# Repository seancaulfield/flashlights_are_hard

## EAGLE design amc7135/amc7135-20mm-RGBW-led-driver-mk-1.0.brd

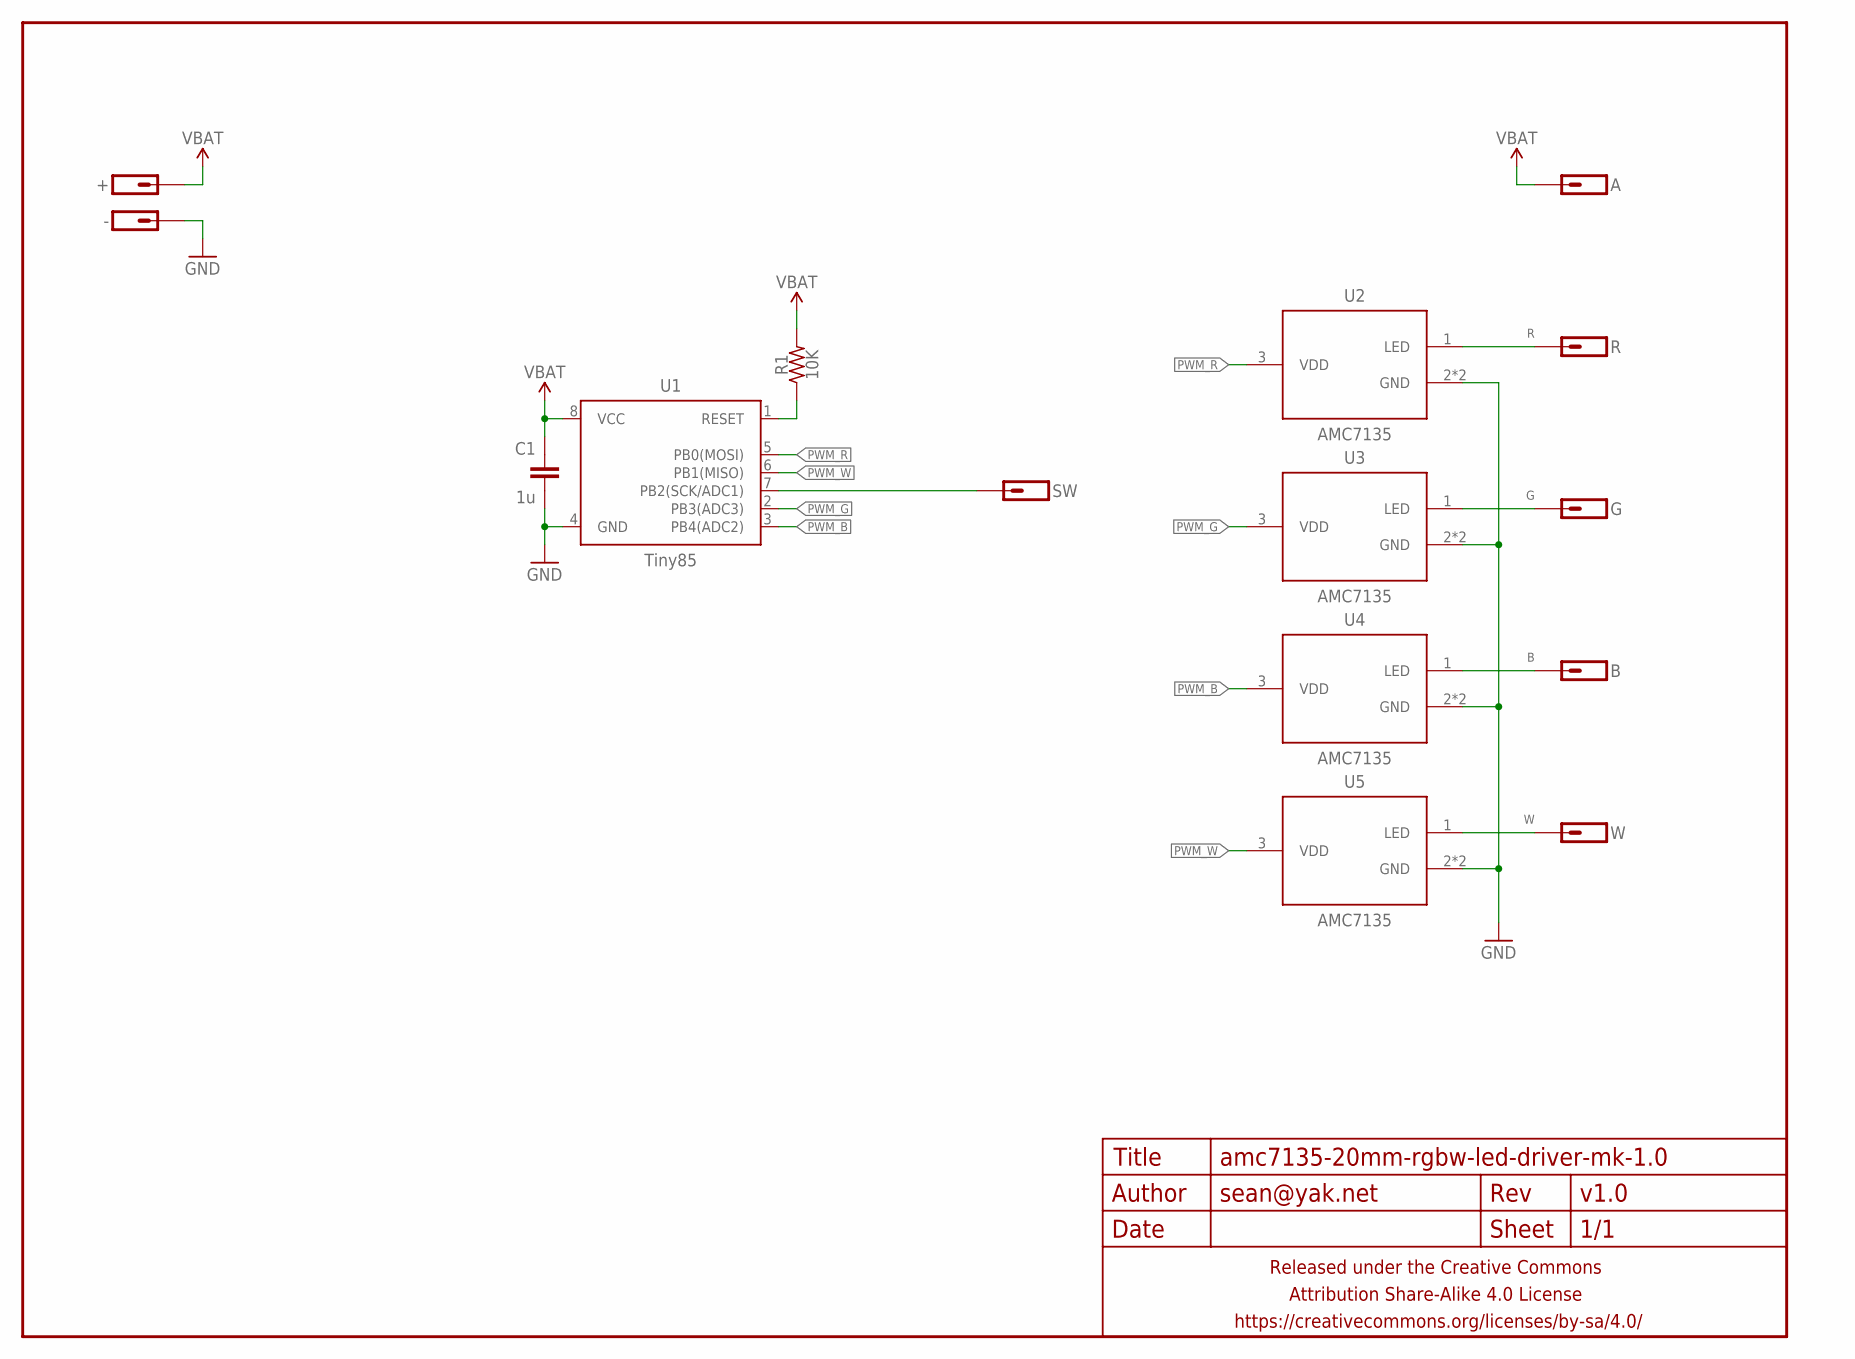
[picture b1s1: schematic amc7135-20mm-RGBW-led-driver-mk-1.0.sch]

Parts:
+: M01NOSTOP-CANTSTOP-DONTKNOWHOWTOSTOP; 1X01_SMD_NOSTOP_NOSILK
-: M01NOT-A-VIA-NOPE; 1X01_NOSILK_NOSTOP
A: M01PTH-1MM-CIR-NS; 1X01-1MM-CIR-NS
B: M01PTH-1MM-CIR-NS; 1X01-1MM-CIR-NS
C1: 1u; C0603-TIGHTER
FRAME1: FRAME-LETTERNO_PACKAGE; DUMMY
G: M01PTH-1MM-CIR-NS; 1X01-1MM-CIR-NS
R: M01PTH-1MM-CIR-NS; 1X01-1MM-CIR-NS
R1: 10K; R0603-TIGHTER
SW: M01PTH-0.8MM; 1X01-0.8MM
U1: Tiny85; SO08-EIAJ
U2, U3, U4, U5: AMC7135; SOT89
W: M01PTH-1MM-CIR-NS; 1X01-1MM-CIR-NS

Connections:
B: B.1, U4.1 (LED)
G: G.1, U3.1 (LED)
GND: -.P$1, C1.2, U1.4 (GND), U2.2 (GND), U2.4 (GND), U3.2 (GND), U3.4 (GND), U4.2 (GND), U4.4 (GND), U5.2 (GND), U5.4 (GND)
unnamed: SW.1, U1.7 (PB2(SCK/ADC1))
unnamed: R1.1, U1.1 (RESET)
PWM_B: U1.3 (PB4(ADC2)), U4.3 (VDD)
PWM_G: U1.2 (PB3(ADC3)), U3.3 (VDD)
PWM_R: U1.5 (PB0(MOSI)), U2.3 (VDD)
PWM_W: U1.6 (PB1(MISO)), U5.3 (VDD)
R: R.1, U2.1 (LED)
VBAT: +.1, A.1, C1.1, R1.2, U1.8 (VCC)
W: U5.1 (LED), W.1

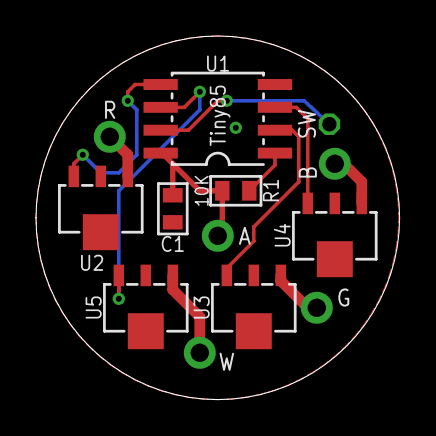
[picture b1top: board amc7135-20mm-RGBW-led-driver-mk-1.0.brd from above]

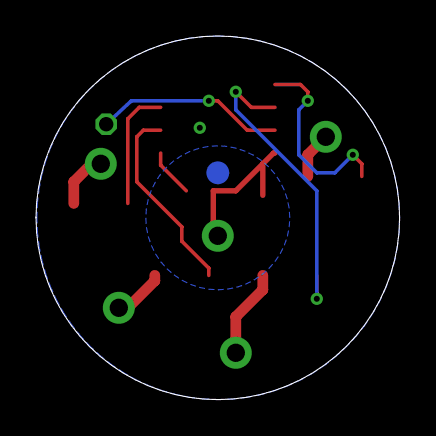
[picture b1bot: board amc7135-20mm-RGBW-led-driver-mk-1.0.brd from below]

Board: 2 copper layers, 20.2 x 20.2 mm, 16 parts (2 on the bottom side), 12 nets.

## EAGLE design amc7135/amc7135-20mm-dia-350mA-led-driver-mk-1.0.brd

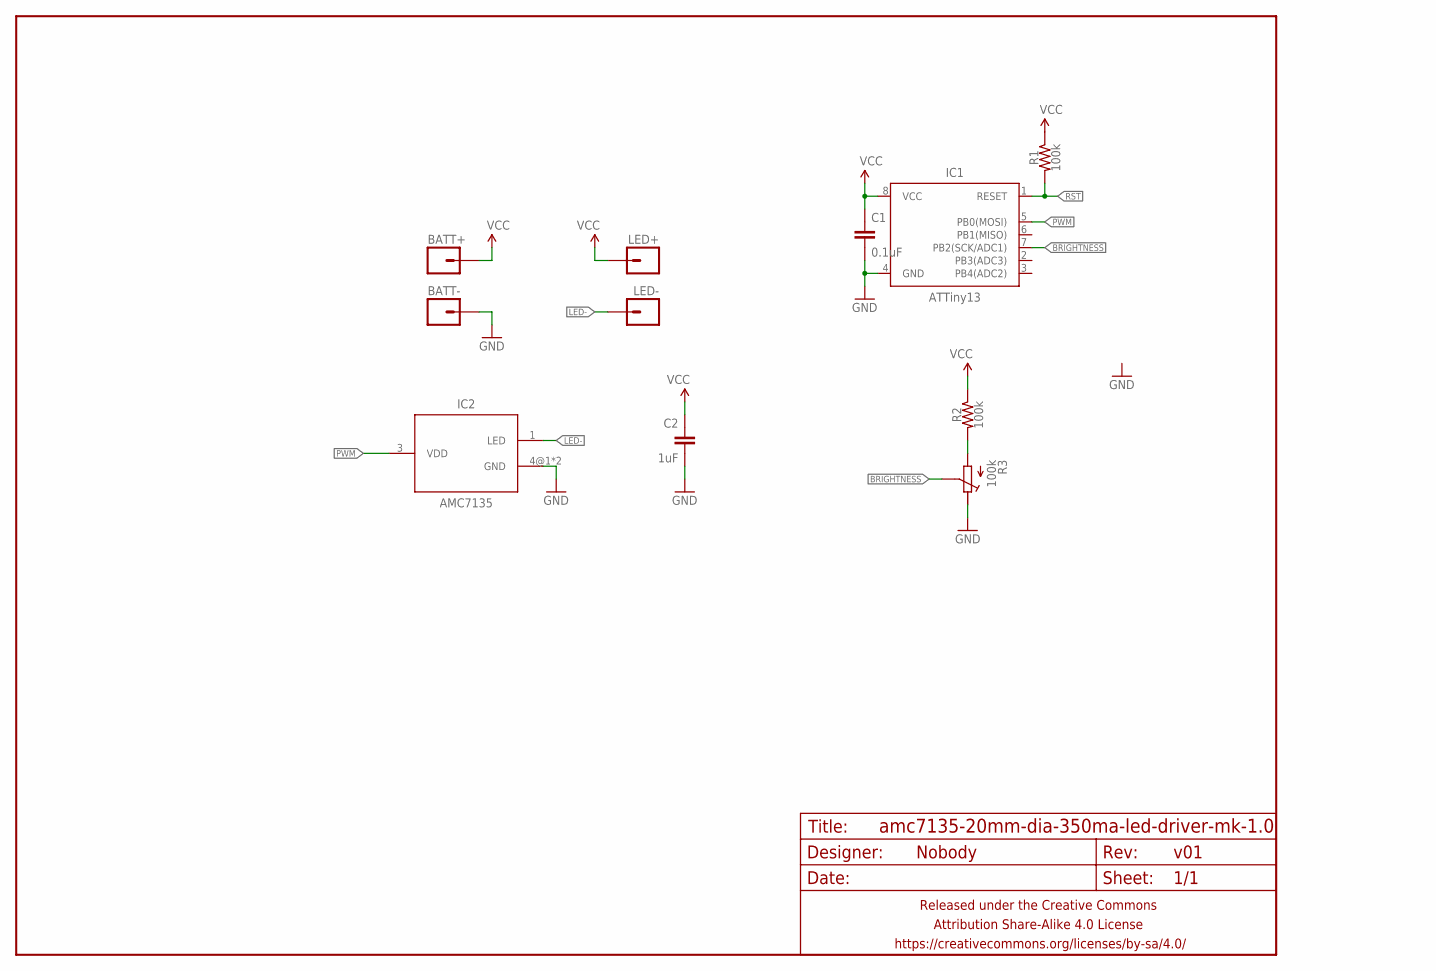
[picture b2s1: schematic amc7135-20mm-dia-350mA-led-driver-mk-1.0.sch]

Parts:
BATT+: M01NOT-A-VIA-NOPE; 1X01_NOSILK_NOSTOP
BATT-: M01NOT-A-VIA-NOPE; 1X01_NOSILK_NOSTOP
C1: 0.1uF; C0805
C2: 1uF; C1206
FRAME1: FRAME-LETTERNO_PACKAGE; DUMMY
IC1: ATTiny13; SO08
IC2: AMC7135; SOT89-NOTHERM
LED+: M01PTH-1.2MM; 1X01-1.2MM
LED-: M01PTH-1.2MM-NS; 1X01-1.2MM-NS
R1, R2: 100k; R0805
R3: 100k; EVM3Y

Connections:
BRIGHTNESS: IC1.7 (PB2(SCK/ADC1)), R3.S
GND: BATT-.P$1, C1.2, C2.2, IC1.4 (GND), IC2.4@1 (GND), IC2.4@2 (GND), R3.E
LED-: IC2.1 (LED), LED-.P$1
unnamed: R2.2, R3.A
PWM: IC1.5 (PB0(MOSI)), IC2.3 (VDD)
RST: IC1.1 (RESET), R1.2
VCC: BATT+.P$1, C1.1, C2.1, IC1.8 (VCC), LED+.P$1, R1.1, R2.1

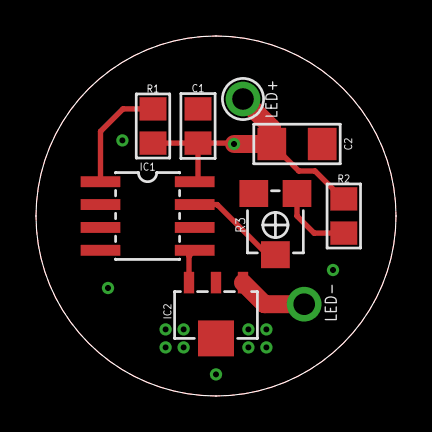
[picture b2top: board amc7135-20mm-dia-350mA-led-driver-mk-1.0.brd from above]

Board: 2 copper layers, 20.0 x 20.0 mm, 12 parts (0 on the bottom side), 7 nets.

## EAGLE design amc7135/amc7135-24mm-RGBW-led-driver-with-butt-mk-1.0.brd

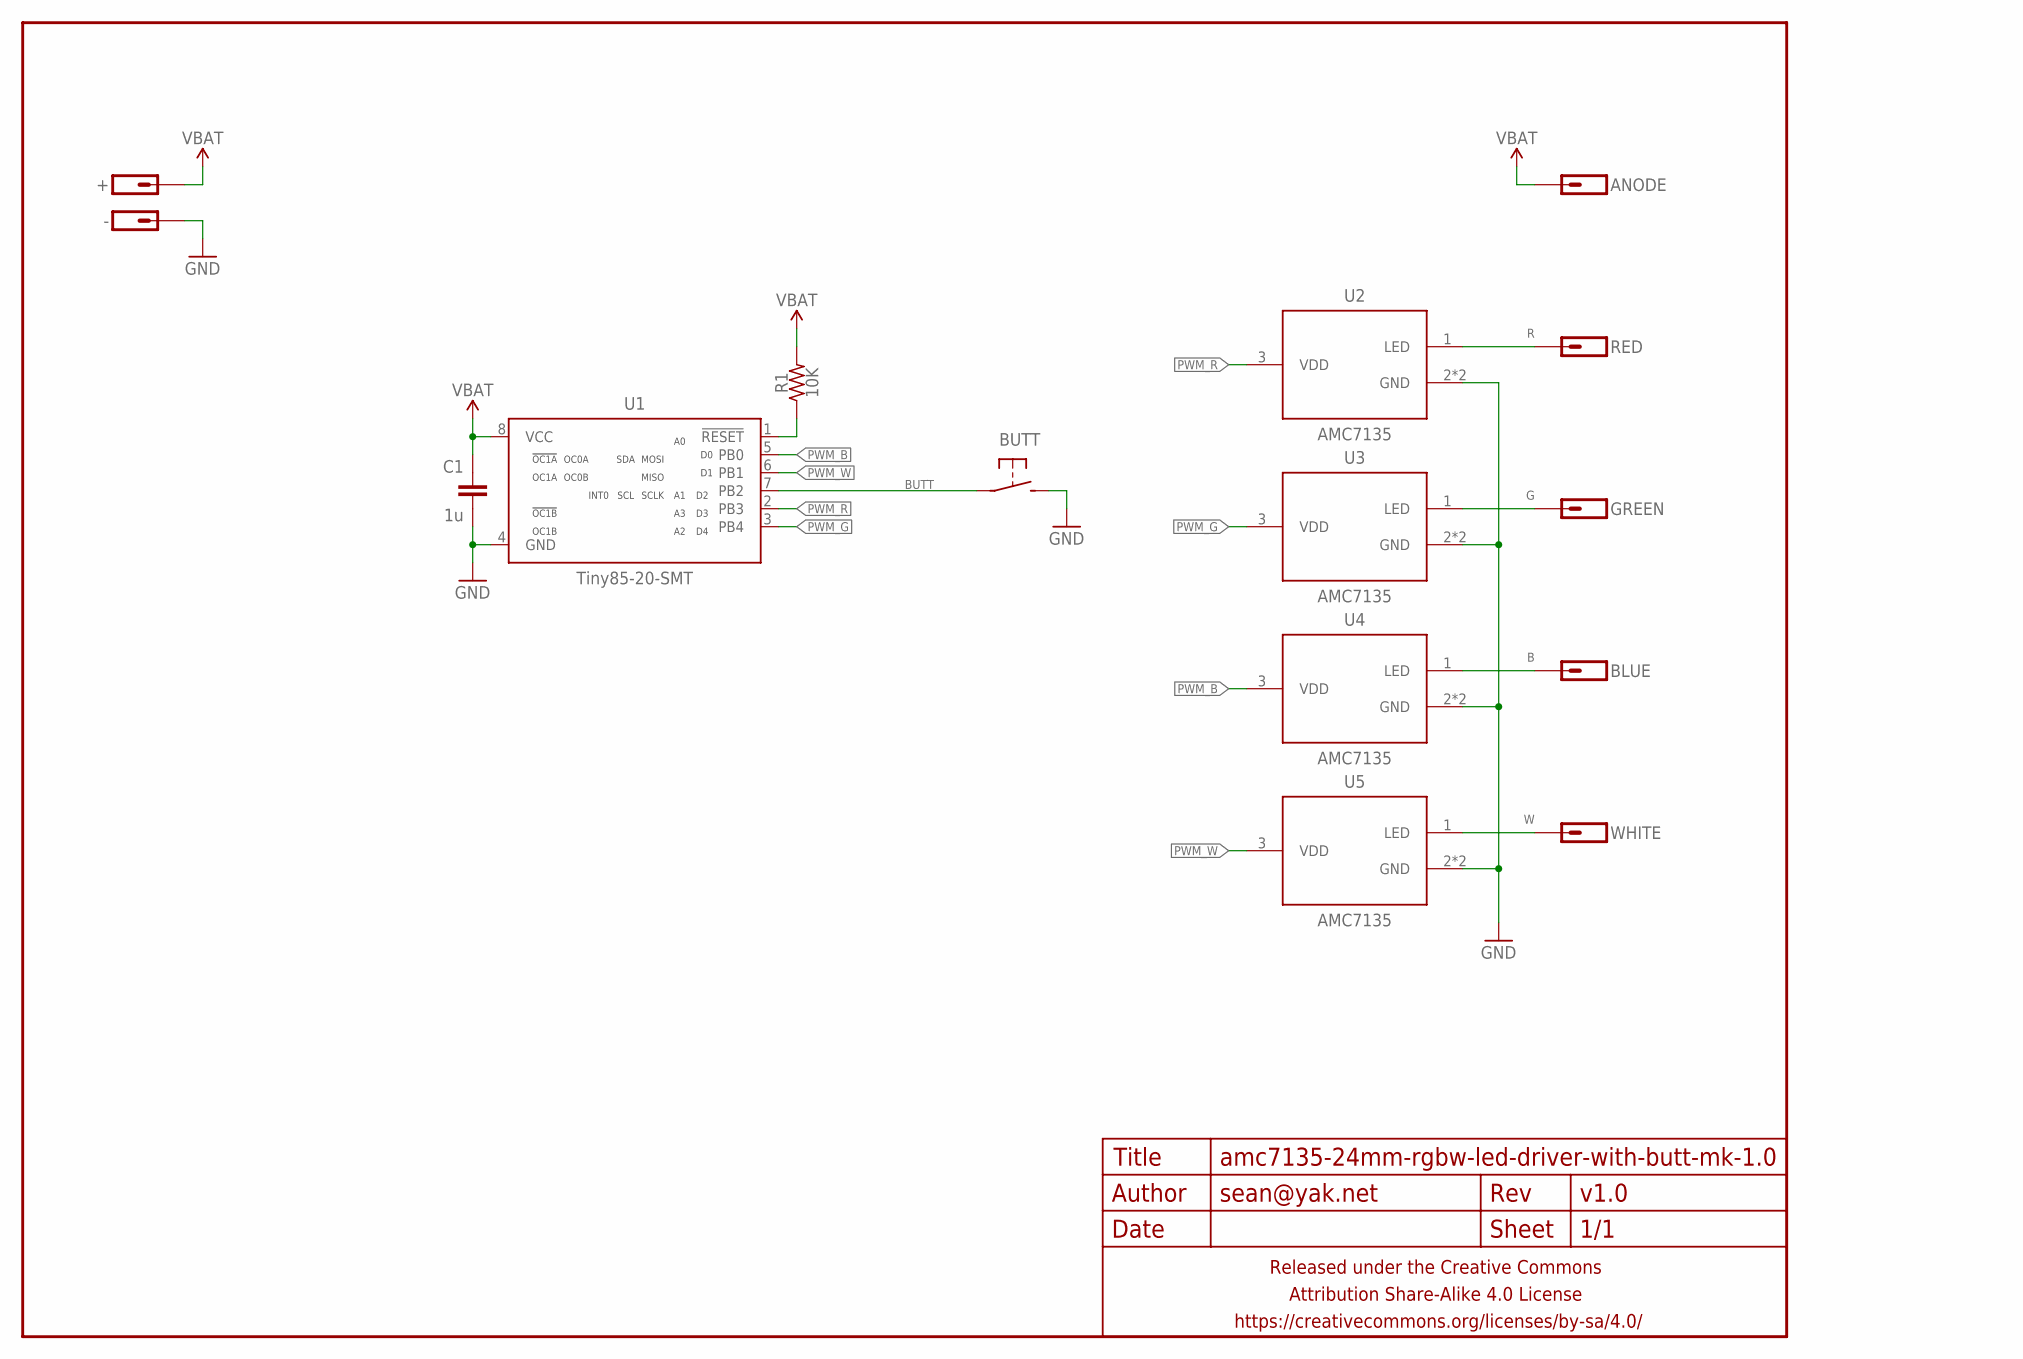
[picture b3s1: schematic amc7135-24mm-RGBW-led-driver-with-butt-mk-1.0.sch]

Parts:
+: M01NOSTOP-CANTSTOP-DONTKNOWHOWTOSTOP; 1X01_SMD_NOSTOP_NOSILK
-: M01NOT-A-VIA-NOPE; 1X01_NOSILK_NOSTOP
ANODE: M01PTH-1.2MM-NS; 1X01-1.2MM-NS
BLUE: M01PTH-1MM-CIR-NS; 1X01-1MM-CIR-NS
BUTT: SPST-NO-TACT3MM-RA; TACTILE-PTH-SIDE
C1: 1u; C0402
FRAME1: FRAME-LETTERNO_PACKAGE; DUMMY
GREEN: M01PTH-1MM-CIR-NS; 1X01-1MM-CIR-NS
R1: 10K; R0402
RED: M01PTH-1MM-CIR-NS; 1X01-1MM-CIR-NS
U1: Tiny85-20-SMT; SO08-EIAJ
U2, U3, U4, U5: AMC7135; SOT89
WHITE: M01PTH-1MM-CIR-NS; 1X01-1MM-CIR-NS

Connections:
B: BLUE.1, U4.1 (LED)
BUTT: BUTT.1, U1.7 (PB2)
G: GREEN.1, U3.1 (LED)
GND: -.P$1, BUTT.2, C1.2, U1.4 (GND), U2.2 (GND), U2.4 (GND), U3.2 (GND), U3.4 (GND), U4.2 (GND), U4.4 (GND), U5.2 (GND), U5.4 (GND)
unnamed: R1.1, U1.1 (!RESET)
PWM_B: U1.5 (PB0), U4.3 (VDD)
PWM_G: U1.3 (PB4), U3.3 (VDD)
PWM_R: U1.2 (PB3), U2.3 (VDD)
PWM_W: U1.6 (PB1), U5.3 (VDD)
R: RED.1, U2.1 (LED)
VBAT: +.1, ANODE.P$1, C1.1, R1.2, U1.8 (VCC)
W: U5.1 (LED), WHITE.1

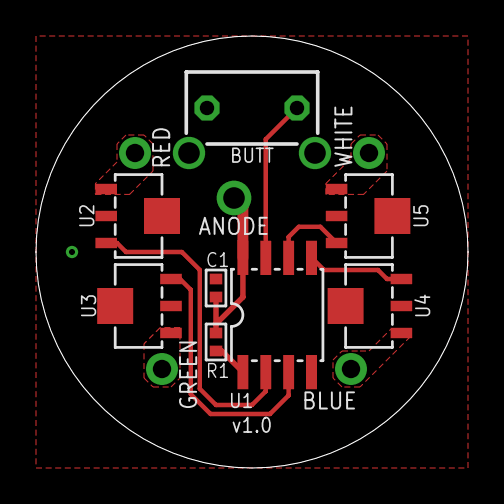
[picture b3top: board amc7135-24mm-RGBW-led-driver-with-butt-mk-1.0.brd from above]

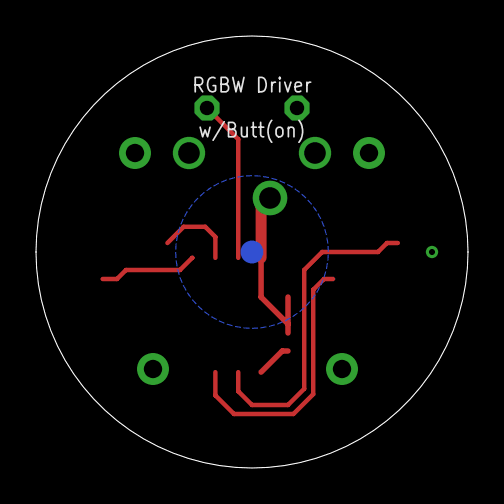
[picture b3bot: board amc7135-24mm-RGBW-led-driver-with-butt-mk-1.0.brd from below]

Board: 2 copper layers, 24.0 x 24.0 mm, 16 parts (2 on the bottom side), 12 nets.

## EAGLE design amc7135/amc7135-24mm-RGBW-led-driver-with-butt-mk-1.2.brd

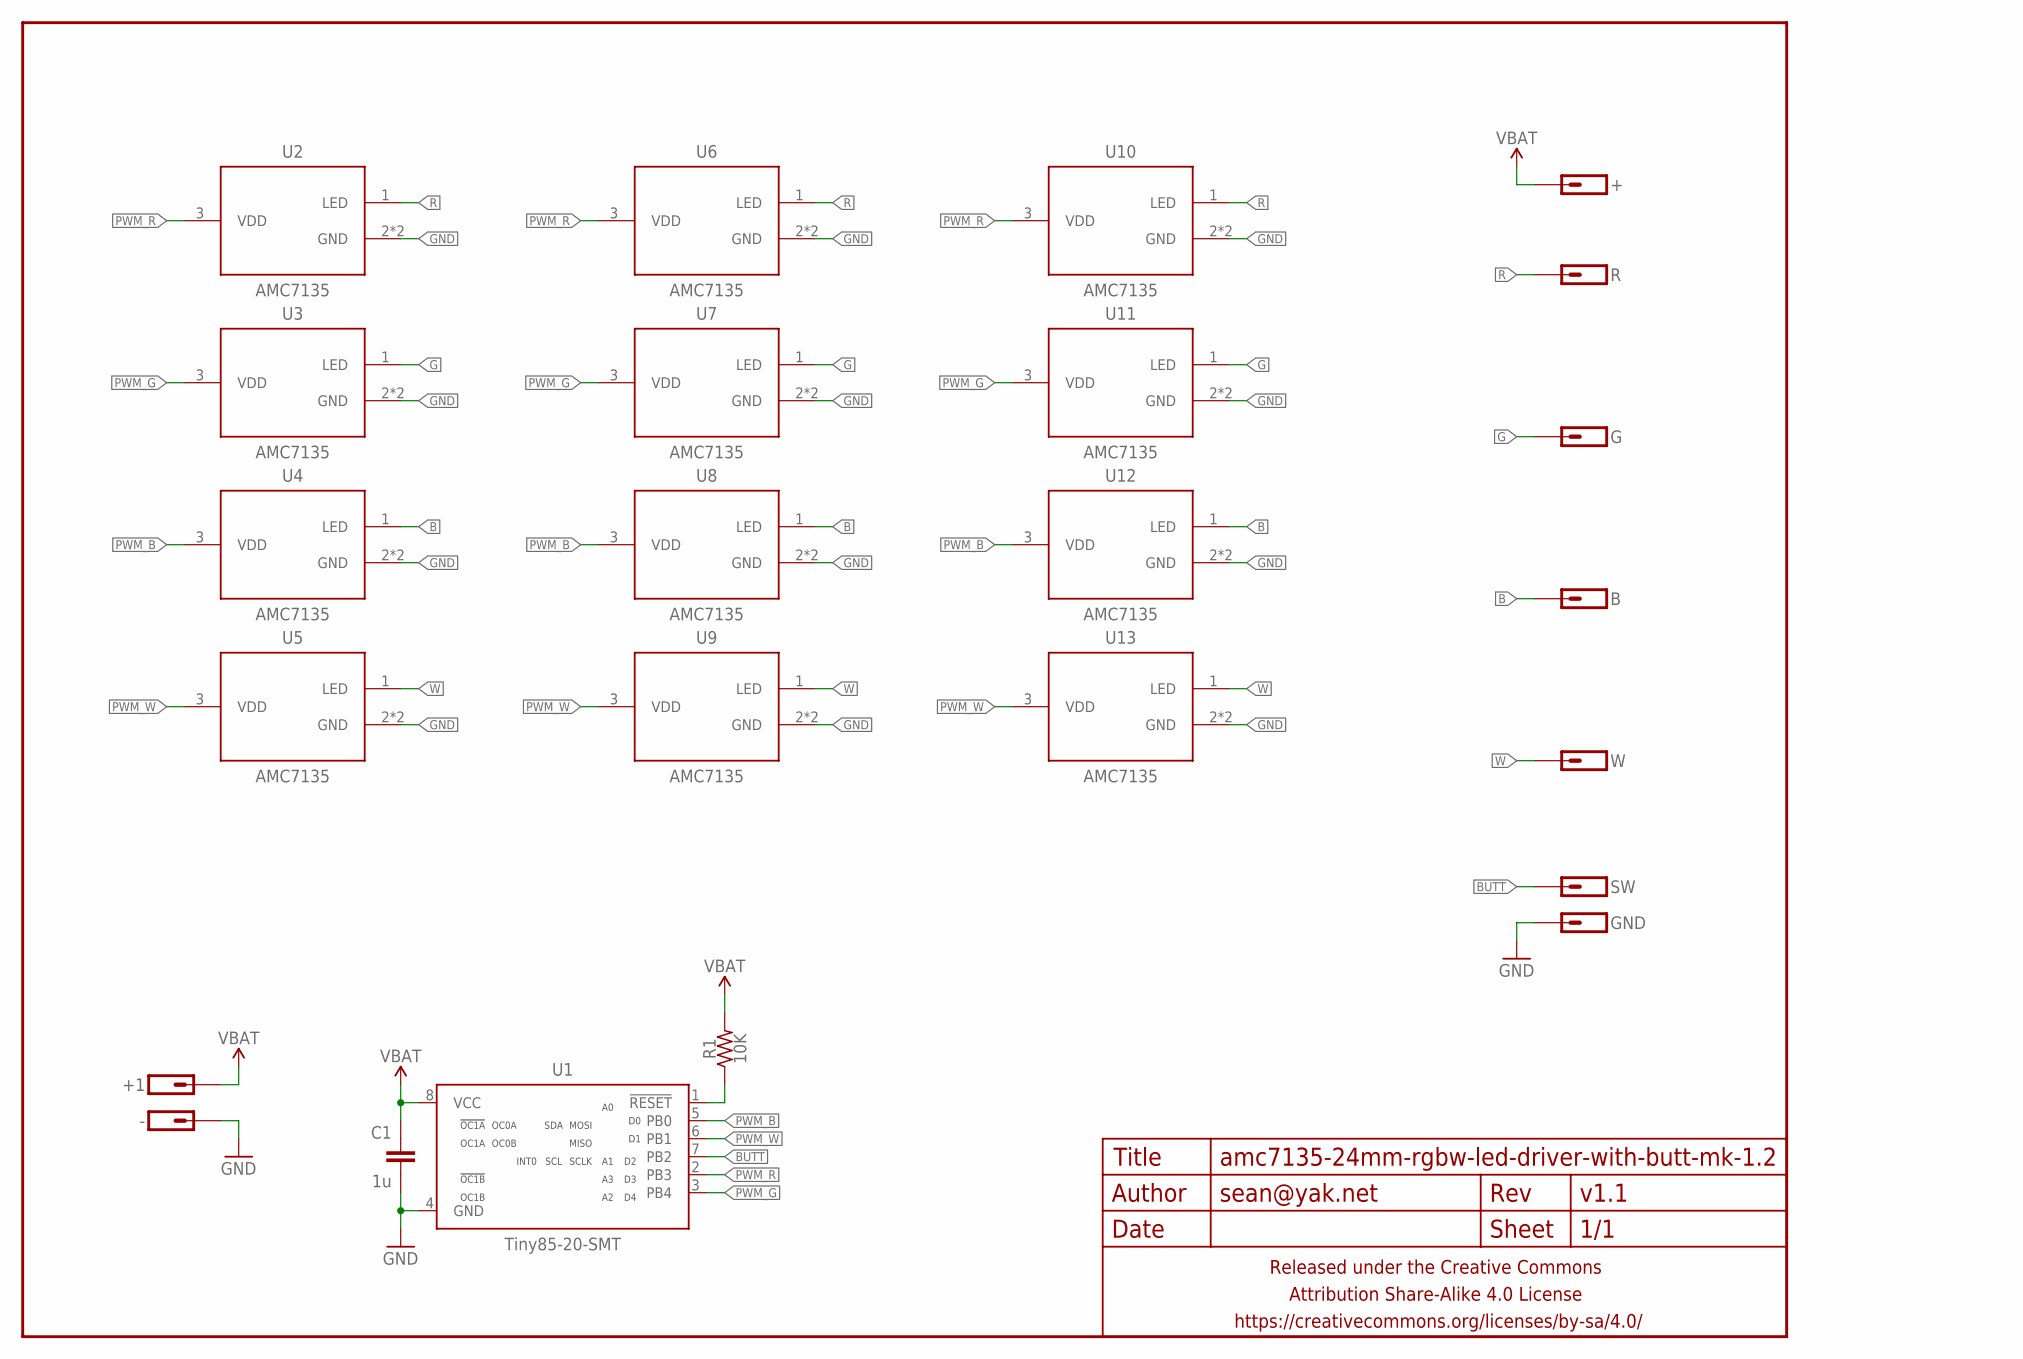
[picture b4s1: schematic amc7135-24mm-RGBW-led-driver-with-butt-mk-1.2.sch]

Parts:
+: M01PTH-1.2MM-NS; 1X01-1.2MM-NS
+1: M01NOSTOP-CANTSTOP-DONTKNOWHOWTOSTOP; 1X01_SMD_NOSTOP_NOSILK
-: M01NOT-A-VIA-NOPE; 1X01_NOSILK_NOSTOP
B: M01SMD-1.25MM-DIA; 1X01-SMD-1.25MM-DIA-NS
C1: 1u; C0603-TIGHTER
FRAME1: FRAME-LETTERNO_PACKAGE; DUMMY
G: M01SMD-1.25MM-DIA; 1X01-SMD-1.25MM-DIA-NS
GND: M01PTH-0.8MM; 1X01-0.8MM
R: M01SMD-1.25MM-DIA; 1X01-SMD-1.25MM-DIA-NS
R1: 10K; R0603-TIGHTER
SW: M01PTH-0.8MM; 1X01-0.8MM
U1: Tiny85-20-SMT; SO08-EIAJ
U2, U3, U4, U5, U6, U7, U8, U9, U10, U11, U12, U13: AMC7135; SOT89
W: M01SMD-1.25MM-DIA; 1X01-SMD-1.25MM-DIA-NS

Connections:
B: B.P$1, U8.1 (LED)
BUTT: SW.1, U1.7 (PB2)
G: G.P$1, U7.1 (LED)
GND: -.P$1, C1.2, GND.1, U1.4 (GND), U6.2 (GND), U6.4 (GND), U7.2 (GND), U7.4 (GND), U8.2 (GND), U8.4 (GND), U9.2 (GND), U9.4 (GND)
unnamed: R1.1, U1.1 (!RESET)
PWM_B: U1.5 (PB0), U4.3 (VDD), U8.3 (VDD), U12.3 (VDD)
PWM_G: U1.3 (PB4), U3.3 (VDD), U7.3 (VDD), U11.3 (VDD)
PWM_R: U1.2 (PB3), U2.3 (VDD), U6.3 (VDD), U10.3 (VDD)
PWM_W: U1.6 (PB1), U5.3 (VDD), U9.3 (VDD), U13.3 (VDD)
R: R.P$1, U6.1 (LED)
VBAT: +.P$1, +1.1, C1.1, R1.2, U1.8 (VCC)
W: U9.1 (LED), W.P$1

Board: 2 copper layers, 25 parts (2 on the bottom side), 12 nets, no tracks yet.

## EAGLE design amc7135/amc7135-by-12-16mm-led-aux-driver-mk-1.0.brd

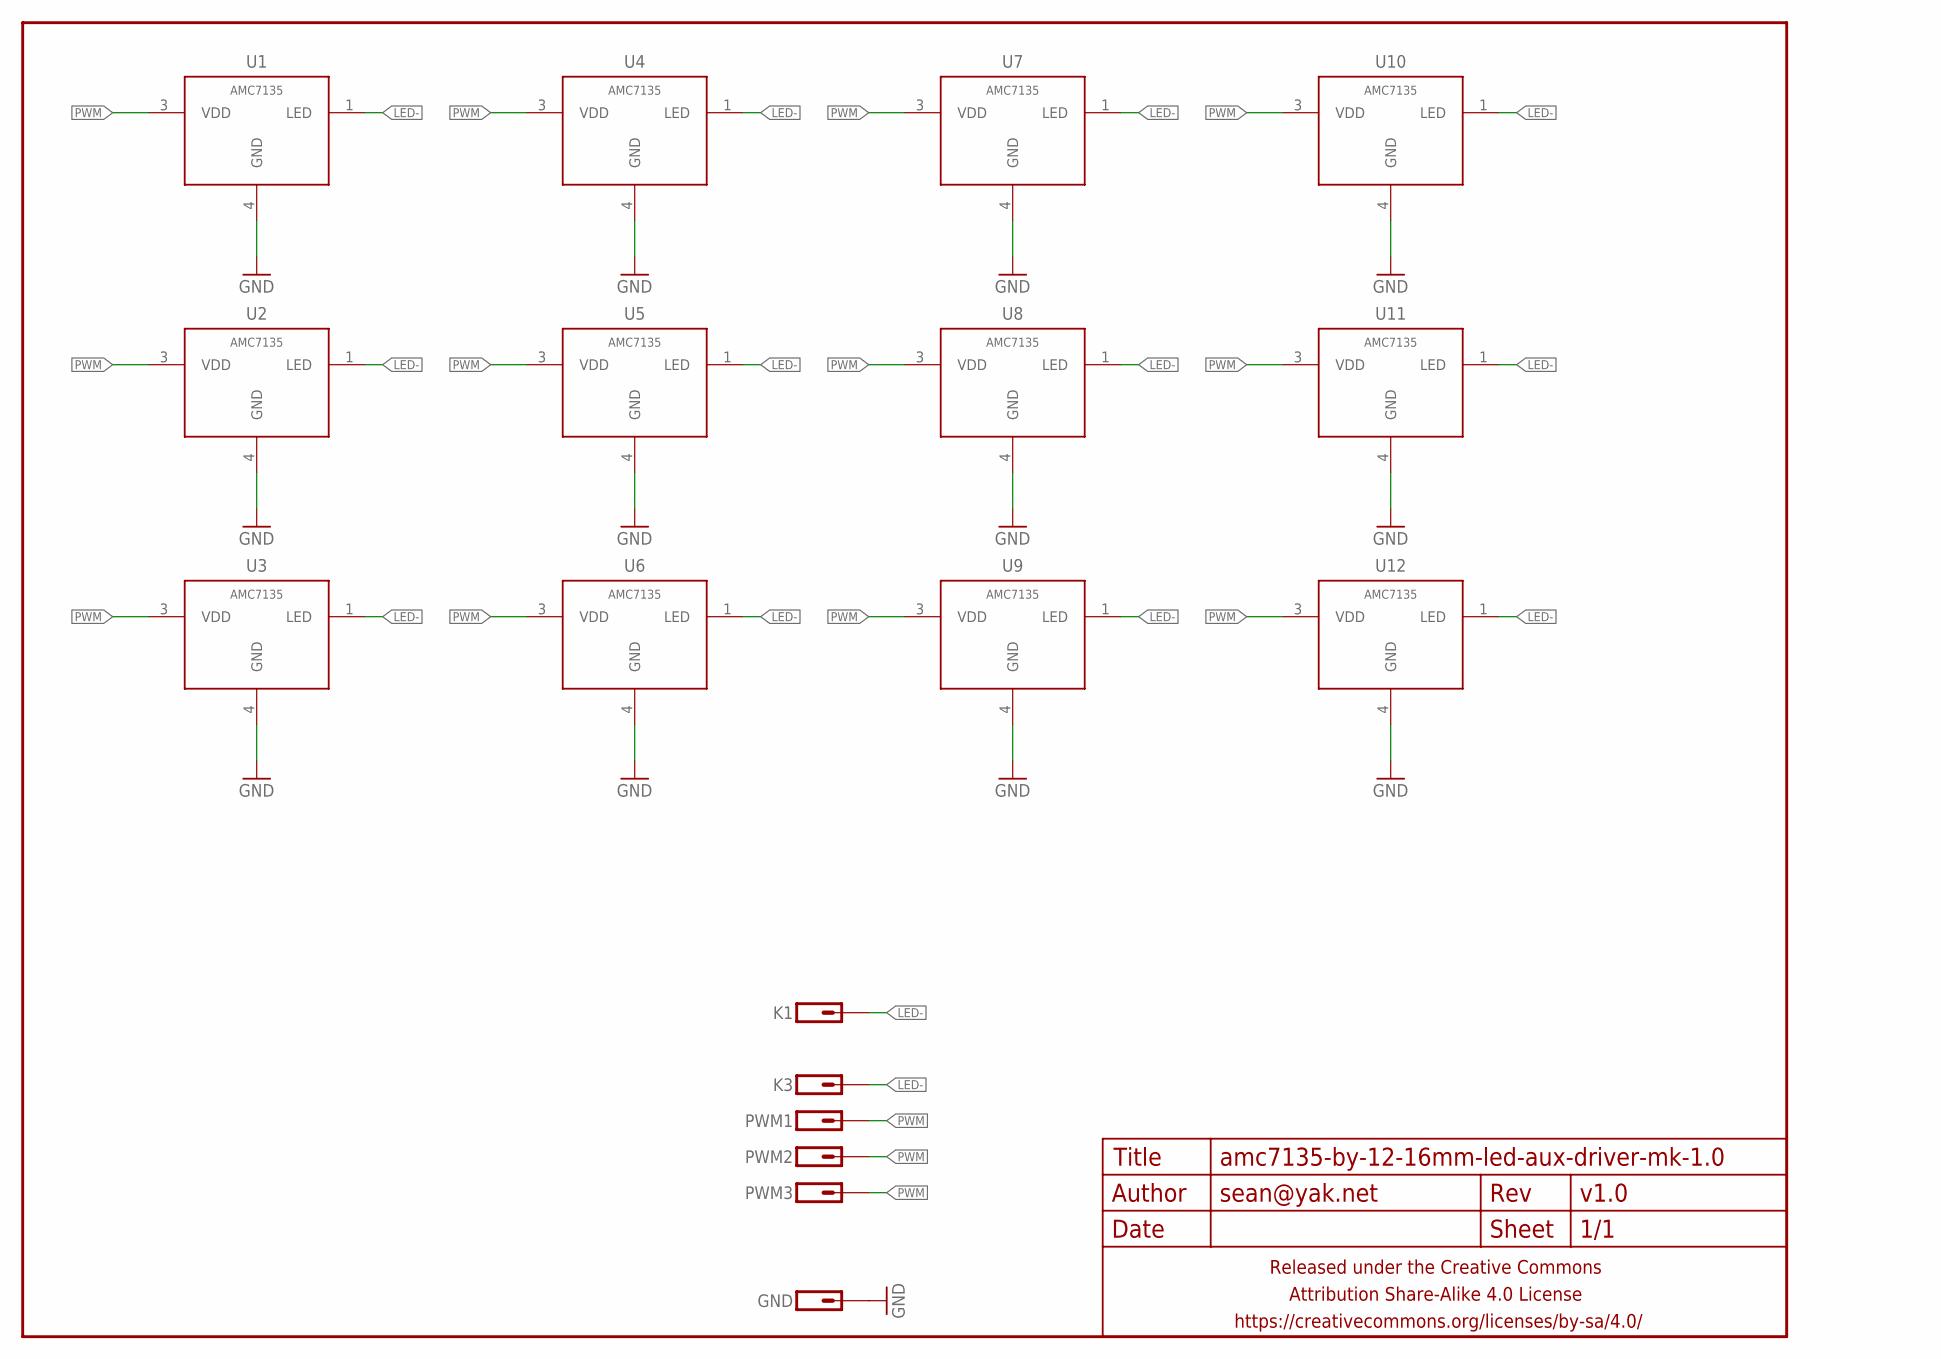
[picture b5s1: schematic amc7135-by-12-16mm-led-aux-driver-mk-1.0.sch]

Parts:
FRAME1: FRAME-LETTERNO_PACKAGE; DUMMY
GND: M01SMD-1MM-DIA-NS; 1X01-SMD-1MM-DIA-NS
K1: M011X01-0.9MM-CIR; 1X01-0.9MM-CIR
K3: M01SMD-1MM-DIA-NS; 1X01-SMD-1MM-DIA-NS
PWM1, PWM2: M01PTH-0.7MM; 1X01-0.7MM
PWM3: M01SMD-1MM-DIA-NS; 1X01-SMD-1MM-DIA-NS
U1, U2, U3, U4, U5, U6, U7, U8, U9, U10, U11, U12: AMC7135; SOT89-NOTHERM-ROUNDED-LESS

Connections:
GND: GND.P$1, U1.4 (GND), U2.4 (GND), U3.4 (GND), U4.4 (GND), U5.4 (GND), U6.4 (GND), U7.4 (GND), U8.4 (GND), U9.4 (GND), U10.4 (GND), U11.4 (GND), U12.4 (GND)
LED-: K1.P$1, K3.P$1, U1.1 (LED), U2.1 (LED), U3.1 (LED), U4.1 (LED), U5.1 (LED), U6.1 (LED), U7.1 (LED), U8.1 (LED), U9.1 (LED), U10.1 (LED), U11.1 (LED), U12.1 (LED)
PWM: PWM1.1, PWM2.1, PWM3.P$1, U1.3 (VDD), U2.3 (VDD), U3.3 (VDD), U4.3 (VDD), U5.3 (VDD), U6.3 (VDD), U7.3 (VDD), U8.3 (VDD), U9.3 (VDD), U10.3 (VDD), U11.3 (VDD), U12.3 (VDD)

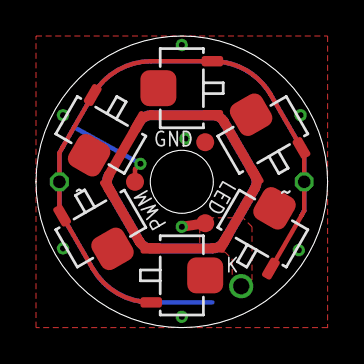
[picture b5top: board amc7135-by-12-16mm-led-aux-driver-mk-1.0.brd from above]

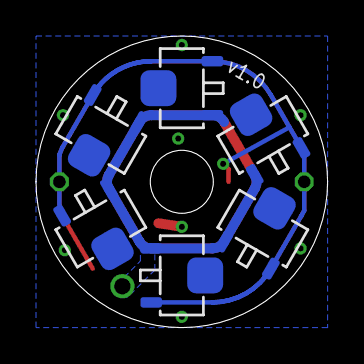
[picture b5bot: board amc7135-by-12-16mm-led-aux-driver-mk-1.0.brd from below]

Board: 2 copper layers, 16.2 x 16.2 mm, 19 parts (6 on the bottom side), 3 nets.

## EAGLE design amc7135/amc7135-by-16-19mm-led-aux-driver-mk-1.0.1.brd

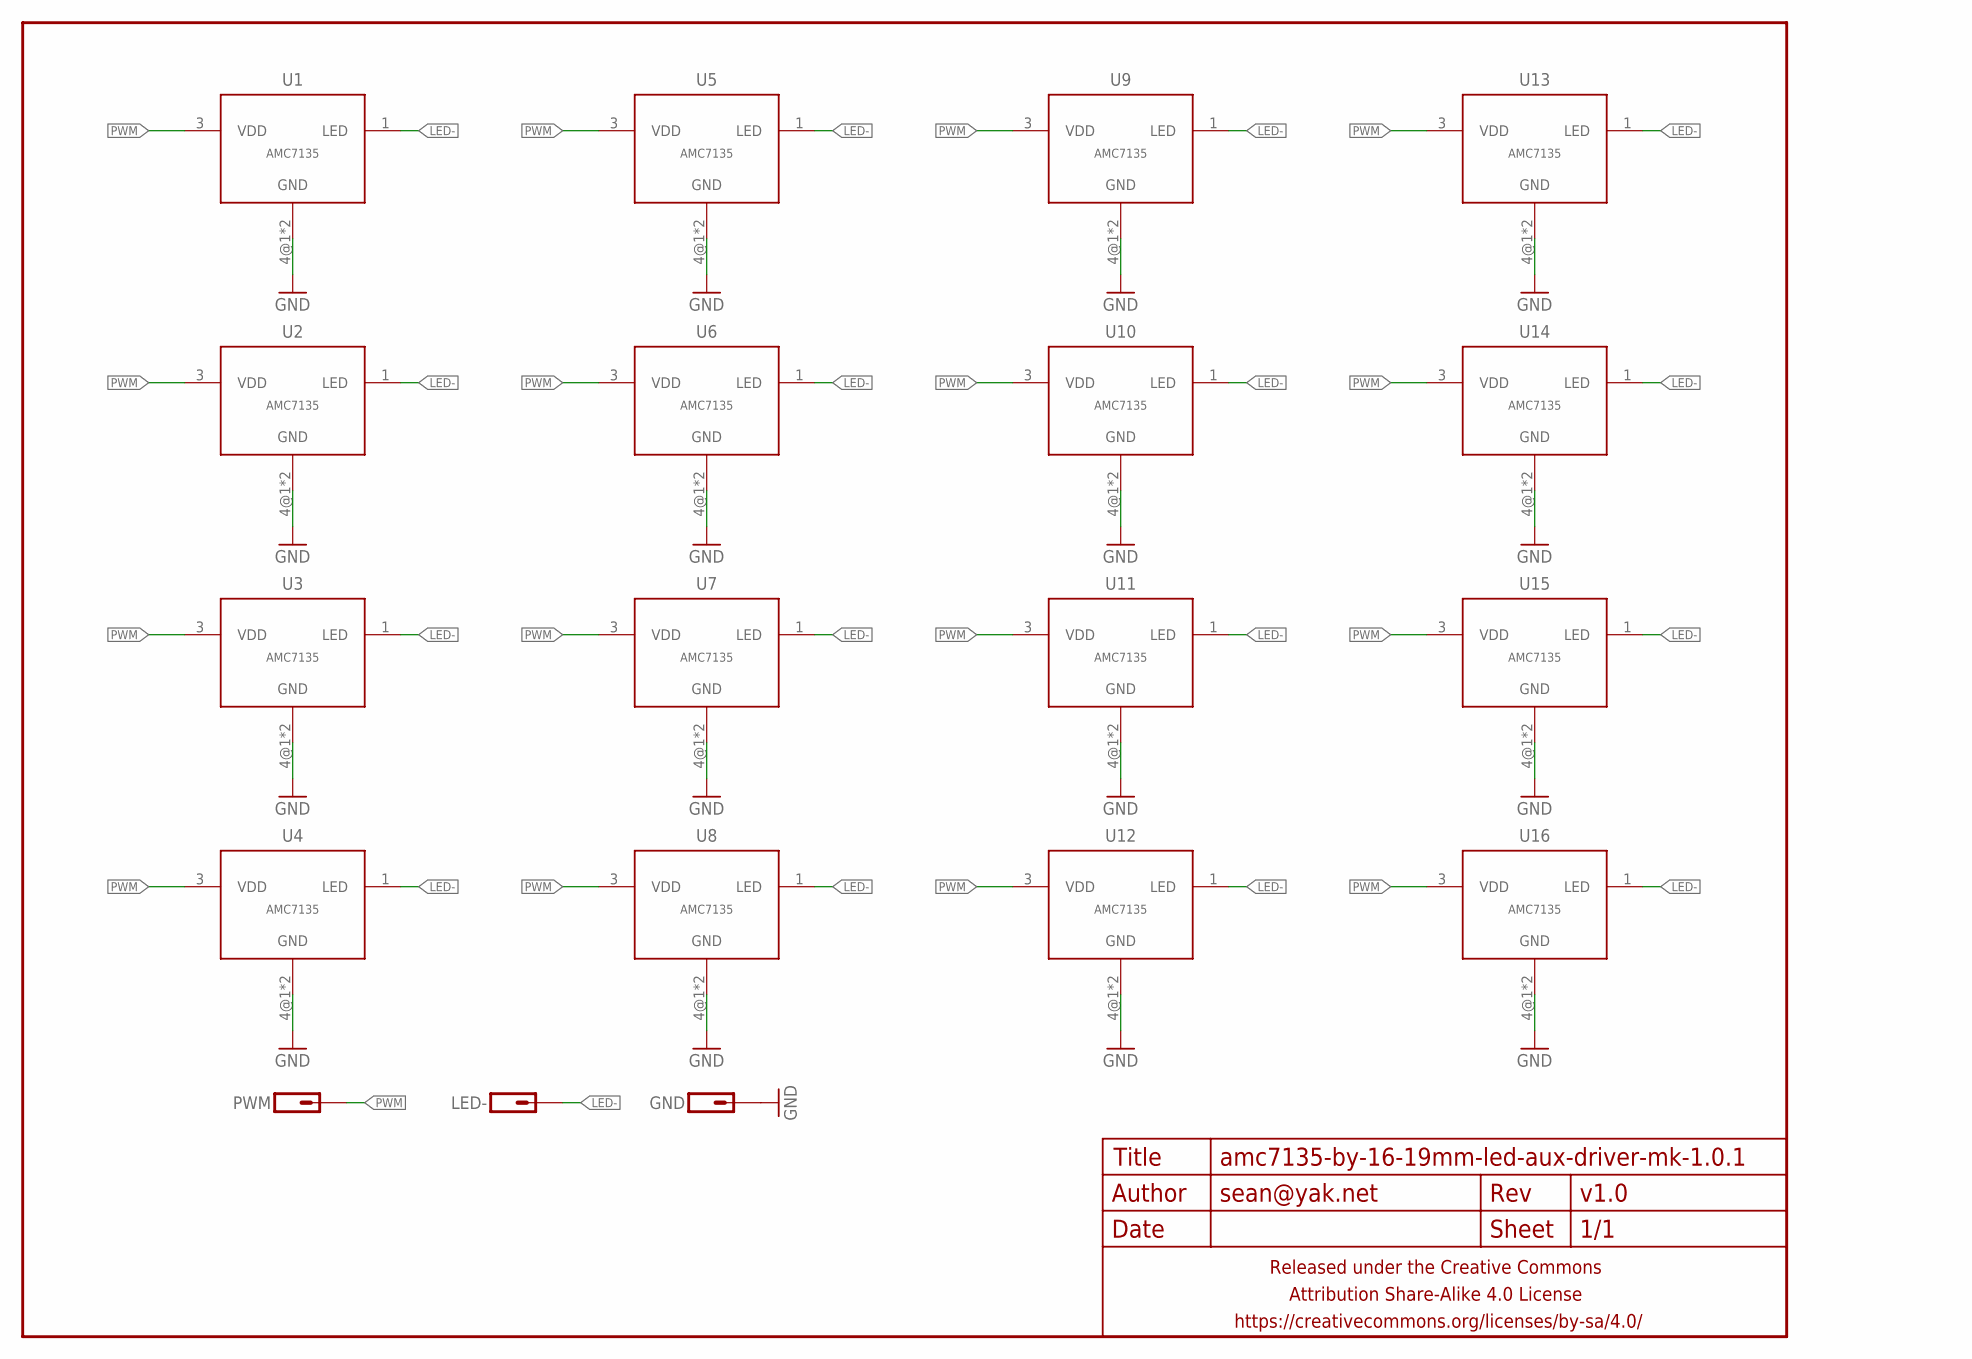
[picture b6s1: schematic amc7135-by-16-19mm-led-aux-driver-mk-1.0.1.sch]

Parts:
FRAME1: FRAME-LETTERNO_PACKAGE; DUMMY
GND: M01PTH-1.2MM-NS; 1X01-1.2MM-NS
LED-: M01PTH-1.2MM-NS; 1X01-1.2MM-NS
PWM: M01PTH-0.9MM-CIR; 1X01-0.9MM-CIR
U1, U2, U3, U4, U5, U6, U7, U8, U9, U10, U11, U12, U13, U14, U15, U16: AMC7135; SOT89-ROUNDED-SMALLER

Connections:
GND: GND.P$1, U1.4@1 (GND), U1.4@2 (GND), U2.4@1 (GND), U2.4@2 (GND), U3.4@1 (GND), U3.4@2 (GND), U4.4@1 (GND), U4.4@2 (GND), U5.4@1 (GND), U5.4@2 (GND), U6.4@1 (GND), U6.4@2 (GND), U7.4@1 (GND), U7.4@2 (GND), U8.4@1 (GND), U8.4@2 (GND), U9.4@1 (GND), U9.4@2 (GND), U10.4@1 (GND), U10.4@2 (GND), U11.4@1 (GND), U11.4@2 (GND), U12.4@1 (GND), U12.4@2 (GND), U13.4@1 (GND), U13.4@2 (GND), U14.4@1 (GND), U14.4@2 (GND), U15.4@1 (GND), U15.4@2 (GND), U16.4@1 (GND), U16.4@2 (GND)
LED-: LED-.P$1, U1.1 (LED), U2.1 (LED), U3.1 (LED), U4.1 (LED), U5.1 (LED), U6.1 (LED), U7.1 (LED), U8.1 (LED), U9.1 (LED), U10.1 (LED), U11.1 (LED), U12.1 (LED), U13.1 (LED), U14.1 (LED), U15.1 (LED), U16.1 (LED)
PWM: PWM.P$1, U1.3 (VDD), U2.3 (VDD), U3.3 (VDD), U4.3 (VDD), U5.3 (VDD), U6.3 (VDD), U7.3 (VDD), U8.3 (VDD), U9.3 (VDD), U10.3 (VDD), U11.3 (VDD), U12.3 (VDD), U13.3 (VDD), U14.3 (VDD), U15.3 (VDD), U16.3 (VDD)

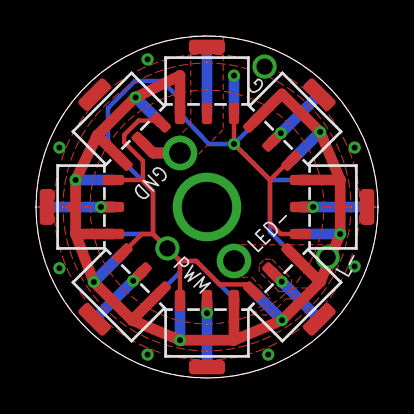
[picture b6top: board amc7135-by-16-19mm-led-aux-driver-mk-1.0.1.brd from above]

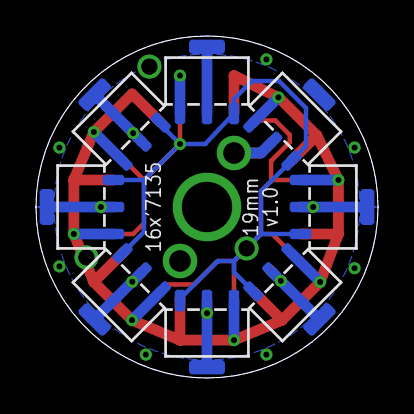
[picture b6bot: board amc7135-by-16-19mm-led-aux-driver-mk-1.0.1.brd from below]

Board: 2 copper layers, 19.0 x 19.0 mm, 20 parts (8 on the bottom side), 3 nets.

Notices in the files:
parts and their libraries:
a_parts: Released under the Creative Commons Attribution Share-Alike 4.0 License
a_parts: https://creativecommons.org/licenses/by-sa/4.0
a_parts: Released under the Creative Commons
